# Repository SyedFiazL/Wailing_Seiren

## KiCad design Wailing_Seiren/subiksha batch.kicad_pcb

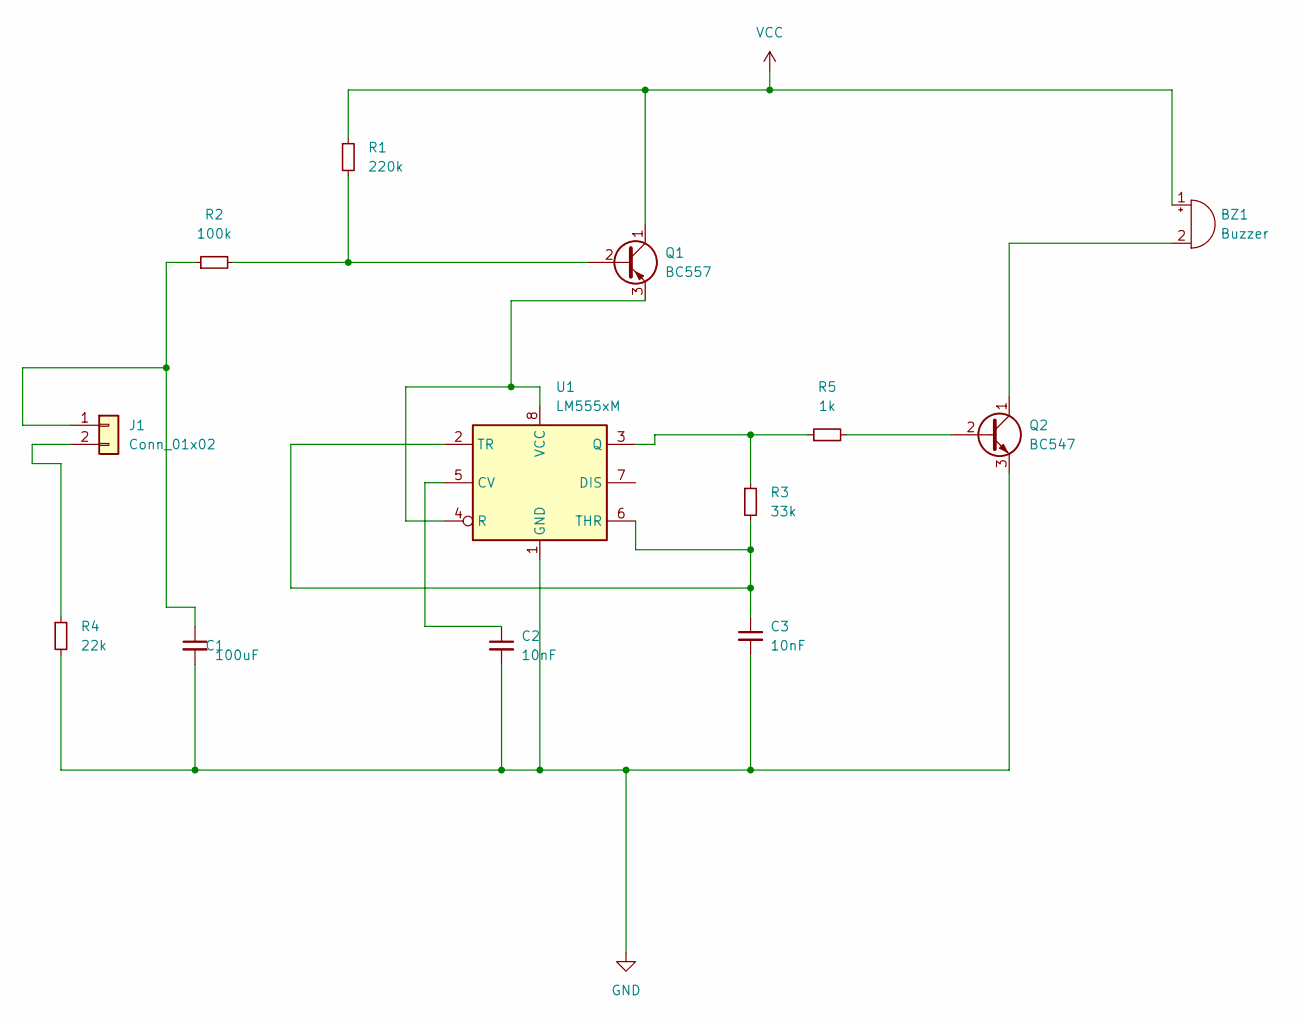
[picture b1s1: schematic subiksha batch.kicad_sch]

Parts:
BZ1: Buzzer; Buzzer_12x9.5RM7.6
C1: 100uF; CP_Axial_L10.0mm_D4.5mm_P15.00mm_Horizontal
C2, C3: 10nF; CP_Axial_L10.0mm_D4.5mm_P15.00mm_Horizontal
J1: Conn_01x02; JWT_A3963_1x02_P3.96mm_Vertical
Q1: BC557; TO-92_Inline
Q2: BC547; TO-92_Inline
R1: 220k; R_Axial_DIN0204_L3.6mm_D1.6mm_P7.62mm_Horizontal
R2: 100k; R_Axial_DIN0204_L3.6mm_D1.6mm_P7.62mm_Horizontal
R3: 33k; R_Axial_DIN0204_L3.6mm_D1.6mm_P7.62mm_Horizontal
R4: 22k; R_Axial_DIN0204_L3.6mm_D1.6mm_P7.62mm_Horizontal
R5: 1k; R_Axial_DIN0204_L3.6mm_D1.6mm_P7.62mm_Horizontal
U1: LM555xM; SOIC-8_3.9x4.9mm_P1.27mm

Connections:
GND: C1.2, C2.2, C3.2, Q2.3 (E), R4.2, U1.1 (GND)
unnamed: BZ1.2 (+), Q2.1 (C)
unnamed: C2.1, U1.5 (CV)
unnamed: J1.2, R4.1
unnamed: Q1.2 (B), R1.2, R2.2
unnamed: Q1.3 (E), U1.4 (R), U1.8 (VCC)
unnamed: C1.1, J1.1, R2.1
unnamed: R3.1, R5.1, U1.3 (Q)
unnamed: C3.1, R3.2, U1.2 (TR), U1.6 (THR)
unnamed: Q2.2 (B), R5.2
VCC: BZ1.1 (-), Q1.1 (C), R1.1

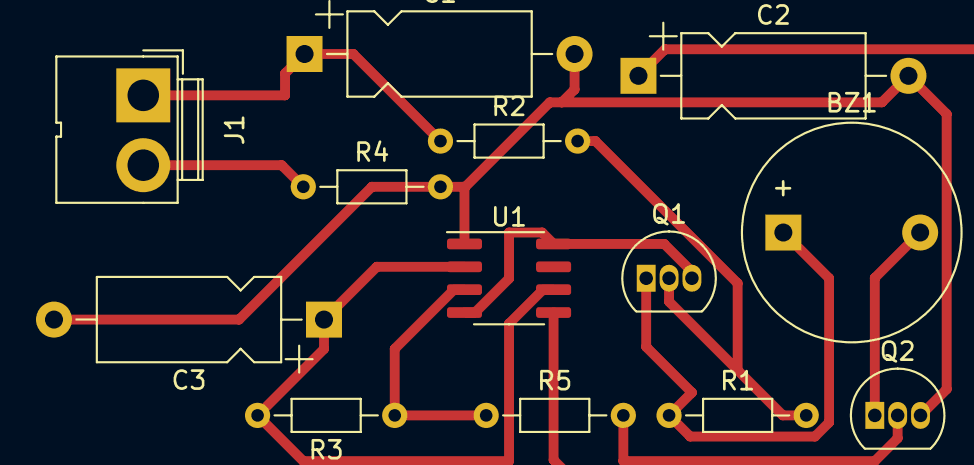
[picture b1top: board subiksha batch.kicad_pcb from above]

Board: 2 copper layers, 13 parts (0 on the bottom side), 11 nets.
